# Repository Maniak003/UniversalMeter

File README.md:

<!DOCTYPE html>
<html lang="en" data-color-mode="auto" data-light-theme="light" data-dark-theme="dark">
  <head>
    <meta charset="utf-8">
  </head>
    <body class="logged-in env-production page-responsive page-blob" style="word-wrap: break-word;">
      <p> Many sensors in one device.</p>
      
    </body>
</html>

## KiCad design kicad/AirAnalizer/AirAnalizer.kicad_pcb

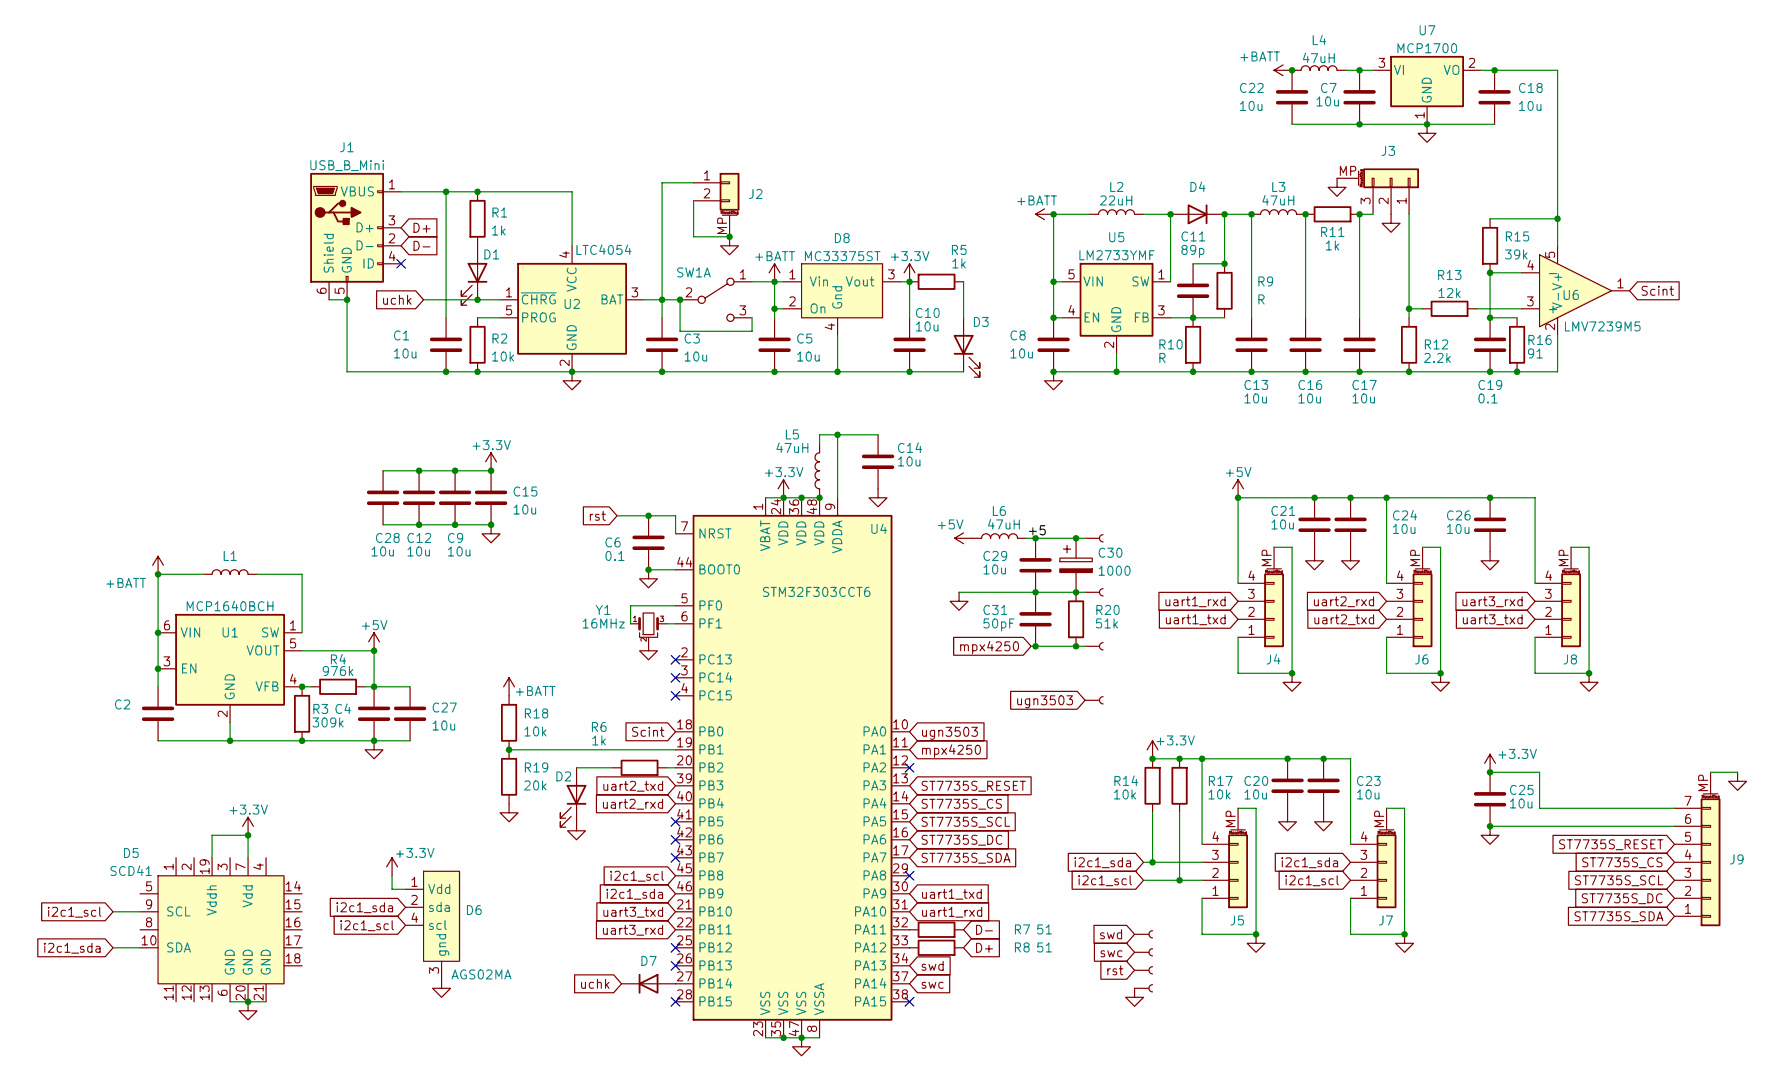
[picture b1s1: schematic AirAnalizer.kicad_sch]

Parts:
C1, C3, C5, C7, C8, C12, C15, C18, C21, C22, C23, C24, C26, C27: 10u; C_0805_2012Metric
C2, C4: C; C_0805_2012Metric
C6, C19: 0.1; C_0603_1608Metric
C9, C10, C14, C20, C25, C28, C29: 10u; C_0603_1608Metric
C11: 89p; C_0603_1608Metric
C13, C16, C17: 10u; C_1210_3225Metric
C30: 1000; CP_EIA-7343-30_AVX-N
C31: 50pF; C_0402_1005Metric
D1, D2, D3: LED; LED_0805_2012Metric
D4: D; D_SOD-123
D5: SCD41
D6: AGS02MA
D7: D; D_SOD-323
D8: MC33375ST; SOT-223
J1: USB_B_Mini; USB_Micro-B_Amphenol_10104110_Horizontal
J2: Conn_01x02_MountingPin; JST_GH_BM02B-GHS-TBT_1x02-1MP_P1.25mm_Vertical
J3: Conn_01x03_MountingPin; JST_GH_BM03B-GHS-TBT_1x03-1MP_P1.25mm_Vertical
J4, J5, J6, J7, J8: Conn_01x04_MountingPin; JST_GH_BM04B-GHS-TBT_1x04-1MP_P1.25mm_Vertical
J9: Conn_01x07_MountingPin; JST_GH_BM07B-GHS-TBT_1x07-1MP_P1.25mm_Vertical
J10, J11, J12, J13, J14, J15, J16: Conn; conn_mini
J17: Conn; mini_conn
L1: 4.7uH; L_Ferrocore_DLG-0403
L2: 22uH; L_1210_3225Metric
L3, L4, L5, L6: 47uH; L_0805_2012Metric
R1, R5, R6, R11: 1k; R_0603_1608Metric
R2, R14, R17, R18: 10k; R_0603_1608Metric
R3: 309k; R_0603_1608Metric
R4: 976k; R_0603_1608Metric
R7, R8: 51; R_0603_1608Metric
R9, R10: R; R_0603_1608Metric
R12: 2.2k; R_0603_1608Metric
R13: 12k; R_0603_1608Metric
R15: 39k; R_0603_1608Metric
R16: 91; R_0603_1608Metric
R19: 20k; R_0603_1608Metric
R20: 51k; R_0402_1005Metric
SW1: SW_DPDT_x2; MySwithc
U1: MCP1640BCH; SOT-23-6
U2: LTC4054; TSOT-23-5
U4: STM32F303CCT6; LQFP-48_7x7mm_P0.5mm
U5: LM2733YMF; SOT-23-5
U6: LMV7239M5; SOT-23-5
U7: MCP1700; SOT-23
Y1: 16MHz; Resonator_SMD_Murata_CSTxExxV-3Pin_3.0x1.1mm

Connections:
+3.3V: C9.1, C10.1, C12.1, C15.1, C20.1, C23.1, C25.1, C28.1, D5.7 (Vdd), D5.19 (Vddh), D6.1 (Vdd), D8.3 (Vout), J5.4, J7.4, J9.7, L5.1, R5.2, R14.2, R17.2, U4.1 (VBAT), U4.24 (VDD), U4.36 (VDD), U4.48 (VDD)
+5V: C4.1, C21.1, C24.1, C26.1, C27.1, J4.4, J6.4, J8.4, L6.1, R4.2, U1.5 (VOUT)
+BATT: C2.1, C5.1, C8.1, C22.1, D8.1 (Vin), D8.2 (On), L1.1, L2.1, L4.1, R18.2, SW1.1 (A), U1.3 (EN), U1.6 (VIN), U5.4 (EN), U5.5 (VIN)
/+5: C29.1, C30.1, J16.1, L6.2
D+: J1.3 (D+), R8.2
D-: J1.2 (D-), R7.2
GND: C1.2, C2.2, C3.2, C4.2, C5.2, C6.2, C7.2, C8.2, C9.2, C10.2, C12.2, C13.2, C14.2, C15.2, C16.2, C17.2, C18.2, C19.2, C20.2, C21.2, C22.2, C23.2, C24.2, C25.2, C26.2, C27.2, C28.2, C29.2, C30.2, C31.1, D2.1 (K), D3.1 (K), D5.6 (GND), D5.20 (GND), D5.21 (GND), D6.3 (gnd), D8.4 (Gnd), J1.5 (GND), J1.6 (Shield), J2.2, J2.MP (MountPin), J3.2, J3.MP (MountPin), J4.1, J4.MP (MountPin), J5.1, J5.MP (MountPin), J6.1, J6.MP (MountPin), J7.1, J7.MP (MountPin), J8.1, J8.MP (MountPin), J9.6, J9.MP (MountPin), J13.1, J15.1, R2.2, R3.2, R10.2, R12.1, R16.2, R19.1, R20.1, U1.2 (GND), U2.2 (GND), U4.8 (VSSA), U4.23 (VSS), U4.35 (VSS), U4.44 (BOOT0), U4.47 (VSS), U5.2 (GND), U6.2 (V-), U7.1 (GND), Y1.2
unnamed: C1.1, J1.1 (VBUS), R1.1, U2.4 (VCC)
unnamed: C3.1, J2.1, SW1.2 (B), SW1.3 (C), U2.3 (BAT)
unnamed: C7.1, L4.2, U7.3 (VI)
unnamed: C11.1, C13.1, D4.1 (K), L3.1, R9.1
unnamed: C11.2, R9.2, R10.1, U5.3 (FB)
unnamed: C14.1, L5.2, U4.9 (VDDA)
unnamed: C16.1, L3.2, R11.1
unnamed: C17.1, J3.3, R11.2
unnamed: C18.1, R15.1, U6.5 (V+), U7.2 (VO)
unnamed: C19.1, R15.2, R16.1, U6.4 (-)
unnamed: D1.2 (A), R1.2
unnamed: D2.2 (A), R6.1
unnamed: D3.2 (A), R5.1
unnamed: D4.2 (A), L2.2, U5.1 (SW)
unnamed: D7.2 (A), U4.27 (PB14)
unnamed: J3.1, R12.2, R13.1
unnamed: L1.2, U1.1 (SW)
unnamed: R2.1, U2.5 (PROG)
unnamed: R3.1, R4.1, U1.4 (VFB)
unnamed: R6.2, U4.20 (PB2)
unnamed: R7.1, U4.32 (PA11)
unnamed: R8.1, U4.33 (PA12)
unnamed: R13.2, U6.3 (+)
unnamed: R18.1, R19.2, U4.19 (PB1)
unnamed: U4.5 (PF0), Y1.1
unnamed: U4.6 (PF1), Y1.3
ST7735S_CS: J9.4, U4.14 (PA4)
ST7735S_DC: J9.2, U4.16 (PA6)
ST7735S_RESET: J9.5, U4.13 (PA3)
ST7735S_SCL: J9.3, U4.15 (PA5)
ST7735S_SDA: J9.1, U4.17 (PA7)
Scint: U4.18 (PB0), U6.1
i2c1_scl: D5.9 (SCL), D6.4 (scl), J5.2, J7.2, R17.1, U4.45 (PB8)
i2c1_sda: D5.10 (SDA), D6.2 (sda), J5.3, J7.3, R14.1, U4.46 (PB9)
mpx4250: C31.2, J14.1, R20.2, U4.11 (PA1)
rst: C6.1, J12.1, U4.7 (NRST)
swc: J11.1, U4.37 (PA14)
swd: J10.1, U4.34 (PA13)
uart1_rxd: J4.3, U4.31 (PA10)
uart1_txd: J4.2, U4.30 (PA9)
uart2_rxd: J6.3, U4.40 (PB4)
uart2_txd: J6.2, U4.39 (PB3)
uart3_rxd: J8.3, U4.22 (PB11)
uart3_txd: J8.2, U4.21 (PB10)
uchk: D1.1 (K), D7.1 (K), U2.1 (~CHRG)
ugn3503: J17.1, U4.10 (PA0)

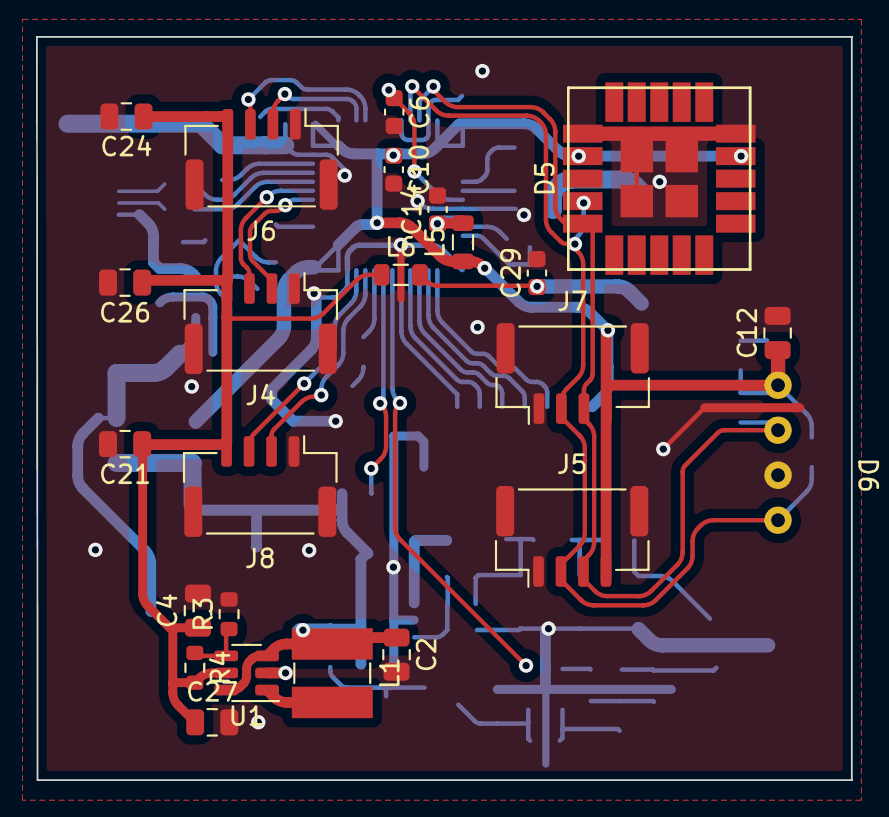
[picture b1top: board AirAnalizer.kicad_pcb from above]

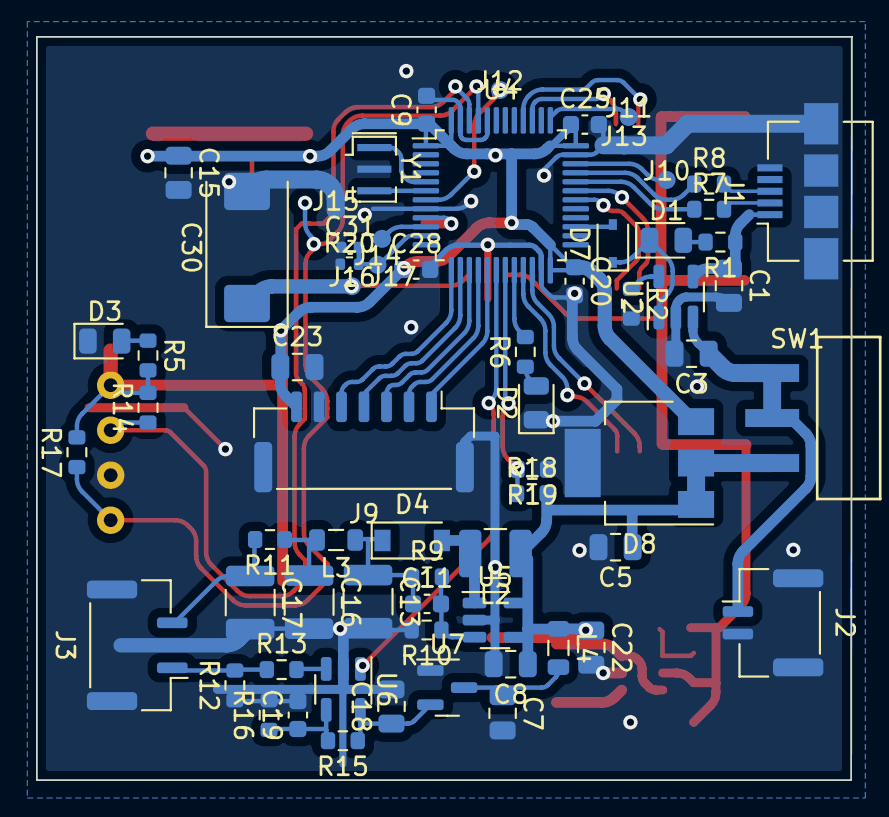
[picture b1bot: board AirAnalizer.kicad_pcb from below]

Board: 2 copper layers, 45.3 x 41.3 mm, 90 parts (66 on the bottom side), 53 nets.

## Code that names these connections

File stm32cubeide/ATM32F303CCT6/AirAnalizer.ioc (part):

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Mcu.Name=STM32F303C(B-C)Tx
Mcu.Package=LQFP48
Mcu.UserName=STM32F303CCTx
PA10.Mode=Asynchronous
PA10.Signal=USART1_RX
PA3.GPIOParameters=GPIO_Label
PA3.GPIO_Label=ST7735S_RESET
PA3.Signal=GPIO_Output
PA4.GPIOParameters=GPIO_Label
PA4.GPIO_Label=ST7735S_CS
PA4.Signal=GPIO_Output
PA5.Mode=TX_Only_Simplex_Unidirect_Master
PA5.Signal=SPI1_SCK
PA6.GPIOParameters=GPIO_Label
PA6.GPIO_Label=ST7735S_DC
PA6.Signal=GPIO_Output
PA7.Mode=TX_Only_Simplex_Unidirect_Master
PA7.Signal=SPI1_MOSI
PA9.Mode=Asynchronous
PA9.Signal=USART1_TX
PB0.Signal=GPXTI0
PB1.GPIOParameters=GPIO_Label
PB1.GPIO_Label=BAT
PB1.Mode=IN1-Single-Ended
PB1.Signal=ADC3_IN1
PB2.GPIOParameters=GPIO_Label
PB2.GPIO_Label=LED
PB2.Signal=GPIO_Output
PB3.GPIOParameters=GPIO_PuPd
PB3.GPIO_PuPd=GPIO_NOPULL
PB3.Mode=Asynchronous
PB3.Signal=USART2_TX
PB4.GPIOParameters=GPIO_PuPd
PB4.GPIO_PuPd=GPIO_NOPULL
PB4.Mode=Asynchronous
PB4.Signal=USART2_RX
PB8.GPIOParameters=GPIO_FM8,GPIO_Pu
PB8.GPIO_FM8=SYSCFG_CFGR1_I2C_PB8_FMP
PB8.GPIO_Pu=GPIO_NOPULL
PB8.Mode=I2C
PB8.Signal=I2C1_SCL
PB9.GPIOParameters=GPIO_Pu,GPIO_FM9
PB9.GPIO_FM9=SYSCFG_CFGR1_I2C_PB9_FMP
PB9.GPIO_Pu=GPIO_NOPULL
PB9.Mode=I2C
PB9.Signal=I2C1_SDA
PF0-OSC_IN.Mode=HSE-External-Oscillator
PF0-OSC_IN.Signal=RCC_OSC_IN
PF1-OSC_OUT.Mode=HSE-External-Oscillator
PF1-OSC_OUT.Signal=RCC_OSC_OUT
RCC.HSEPLLFreq_Value=8000000
RCC.HSE_VALUE=16000000
RCC.SYSCLKFreq_VALUE=72000000
RCC.SYSCLKSourceVirtual=RCC_SYSCLKSOURCE_PLLCLK
board=custom

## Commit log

2024-01-20 новый файл: Documents/MPX4250.PDF новый файл: Documents/PMS5003-Series-Manual.pdf новый файл: Documents/SS49E.pdf новый файл: Documents/UGN3503U.PDF новый файл: "Documents/\320\226\320\265\320\275\32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
2024-01-20 новый файл: kicad/AirAnalizer/AirAnalizer.pdf новый файл: kicad/AirAnalizer/AirAnalizer.png
2024-01-21 изменено: FreeCAD/base.FCStd изменено: FreeCAD/base.FCStd1 удалено: kicad/AirAnalizer/AirAnalizer-backups/AirAnalizer-2023-11-27_121647.zip удалено: kicad/AirAnalizer/AirAnalizer-backups/AirAnalizer-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
2024-01-21 новый файл: FreeCAD/base_top.FCStd новый файл: FreeCAD/cover.FCStd новый файл: FreeCAD/cover.stl новый файл: stm32cubeide/ATM32F303CCT6/Core/Inc/i2c.h новый файл: stm32cubeide/ATM32F303CCT6/Core/Inc/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
2024-01-21 новый файл: Documents/bot_board.png новый файл: Documents/top_board.png изменено: FreeCAD/base.FCStd изменено: FreeCAD/base.FCStd1 изменено: FreeCAD/base.stl новый файл: FreeCAD/base2.stl изменено: F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
2024-03-01 изменено: FreeCAD/base.FCStd изменено: FreeCAD/base.FCStd1 изменено: FreeCAD/base.stl удалено: kicad/AirAnalizer/AirAnalizer-backups/AirAnalizer-2023-12-22_111938.zip
2024-05-10 новый файл: Documents/UniversalMeter.png изменено: README.md
